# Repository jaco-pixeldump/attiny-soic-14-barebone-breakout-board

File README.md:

# ATtiny SOIC-14 Breadboard Breakout Board (tinyAVR-2 / 1 / 0 Series)

> [!NOTE]
> **Notice**: It's a work in progress, small changes are pending.

A compact, breadboard-friendly breakout adapter PCB for **14-pin SOIC Microchip ATtiny** microcontrollers (such as **ATtiny3224, ATtiny1624, ATtiny824, ATtiny424**, as well as 1-series and 0-series parts like **ATtiny1614, ATtiny814, ATtiny414, ATtiny404, ATtiny214, ATtiny204**).

Designed to bridge the gap between SMD SOIC-14 packaging and rapid breadboard prototyping, this board breaks out all 14 pins into a standard 600 mil DIP form factor with onboard decoupling capacitors for noise-free, stable operation.

---

## 3D Render

---

## Features

- **Breadboard Friendly (600 mil DIP Spacing)**: The two 7-pin header rows are spaced at 15.24 mm (0.6" / 600 mil), spanning the center divider of a standard solderless breadboard while leaving tie-points accessible on both sides.
- **Onboard Power Decoupling**:
  - `C1` (**10 nF**, 0805): High-frequency ceramic decoupling capacitor.
  - `C2` (**10 µF**, 0805): Bulk electrolytic/tantalum-replacement ceramic capacitor.
  - Placed directly across $V_{DD}$ (Pin 1) and $\text{GND}$ (Pin 14) to eliminate supply ripple, reduce voltage dips, and prevent brownout resets.
- **Direct 1:1 DIP Pinout**: Headers match the physical DIP-14 pin numbering (Pins 1–7 down the left row, Pins 8–14 down the right row).
- **UPDI Programming Access**: The single-wire UPDI interface on Pin 10 (`PA0 / ~RESET / UPDI`) is broken out directly, enabling instant flashing via SerialUPDI or hardware programmers.
- **Continuous Ground Plane**: Bottom layer is an uninterrupted copper ground pour for solid signal return paths and improved EMI performance.
- **Clear Silkscreen Markings**: Pin 1 orientation triangle, component references, GND reference, and board family indicators clearly printed.

---

## Board Specifications

| Parameter | Value |
|---|---|
| **Dimensions** | 21.06 mm × 19.60 mm (0.83" × 0.77") |
| **Layers** | 2 Layers (FR-4) |
| **Row Pitch** | 15.24 mm (0.600" / 600 mil DIP) |
| **Header Pitch** | 2.54 mm (0.100") |
| **IC Footprint** | SOIC-14 (3.9 mm × 8.7 mm, 1.27 mm pitch) |
| **Passive Footprint** | 0805 Metric (2012) with hand-solder pads |
| **Copper Weight** | 1 oz (35 µm) |
| **Default Board Thickness** | 1.6 mm |

---

## Pinout & Peripheral Mapping

The breakout headers map 1:1 to the SOIC-14 IC pins. The table below lists the pin functions for the modern **ATtiny tinyAVR 2-Series** (ATtiny3224 / ATtiny1624 / ATtiny824 / ATtiny424):

```
                       +---[ SOIC-14 / DIP-14 ]---+
        VDD (+1.8V..5V) [ 1  ]                    [ 14 ] GND
      PA4 (AIN4 / TCA0) [ 2  ]                    [ 13 ] PA3 (AIN3 / EXTCLK)
     PA5 (AIN5 / VREFA) [ 3  ]                    [ 12 ] PA2 (AIN2 / USART0 RX)
      PA6 (AIN6 / TCA0) [ 4  ]                    [ 11 ] PA1 (AIN1 / USART0 TX)
     PA7 (AIN7 / EVOUT) [ 5  ]                    [ 10 ] PA0 (UPDI / ~RESET)
 PB3 (RxD / SCL / TCB0) [ 6  ]                    [  9 ] PB0 (AIN11 / CLKOUT)
 PB2 (TxD / SDA / TCA0) [ 7  ]                    [  8 ] PB1 (AIN10 / TCA0)
                        +--------------------------+
```

### Detailed Pin Table

| Header Pin | IC Pin | Primary Name | Default / Alternate Functions | Notes |
|:---:|:---:|:---|:---|:---|
| **1** | 1 | `VDD` | Power supply (+1.8V to +5.5V) | Decoupled via C1 (10nF) and C2 (10µF) |
| **2** | 2 | `PA4` | AIN4, TCA0 WO4, CCL IN0, USART0 XCK | Digital I/O / Analog input |
| **3** | 3 | `PA5` | AIN5, TCA0 WO5, CCL OUT0, VREFA | Analog reference / PWM |
| **4** | 4 | `PA6` | AIN6, TCA0 WO0, CCL IN1, AC0 OUT | Analog input / PWM |
| **5** | 5 | `PA7` | AIN7, TCA0 WO1, CCL IN2, EVOUT0 | Event output / PWM |
| **6** | 6 | `PB3` | AIN8, TCA0 WO0, TCB0 WO, USART0 RXD, TWI0 SCL | I2C SCL / UART RX |
| **7** | 7 | `PB2` | AIN9, TCA0 WO1, USART0 TXD, TWI0 SDA | I2C SDA / UART TX |
| **8** | 8 | `PB1` | AIN10, TCA0 WO2, USART0 XCK | Digital I/O / Analog input |
| **9** | 9 | `PB0` | AIN11, TCA0 WO2, CLKOUT | Clock output / Analog input |
| **10** | 10 | `PA0` | `~RESET` / `UPDI` | **Programming / Debugging pin** |
| **11** | 11 | `PA1` | AIN1, TCA0 WO1, USART0 TXD | UART Alternate TX / Analog input |
| **12** | 12 | `PA2` | AIN2, TCA0 WO2, USART0 RXD, EVOUT1 | UART Alternate RX / Analog input |
| **13** | 13 | `PA3` | AIN3, TCA0 WO3, EXTCLK | External clock input / Analog input |
| **14** | 14 | `GND` | Ground reference (0V) | Common ground plane connection |

*(Note: Pin functions are also backwards-compatible with tinyAVR 0-series and 1-series SOIC-14 microcontrollers).*

---

## Bill of Materials (BOM)

| Reference | Value | Package / Footprint | Qty | Description | Suggested Part / MPN |
|---|---|---|:---:|---|---|
| **U1** | ATtiny3224-SS | SOIC-14 (3.9x8.7mm, 1.27mm pitch) | 1 | 8-bit AVR Microcontroller (20MHz, 32KB Flash, 3KB SRAM) | `ATTINY3224-SSFR` / `ATTINY1624-SSFR` |
| **C1** | 10 nF (0.01 µF) | 0805 (2012 Metric) | 1 | Ceramic capacitor, 50V, X7R (High-frequency decoupling) | Generic 0805 10nF 50V |
| **C2** | 10 µF | 0805 (2012 Metric) | 1 | Ceramic capacitor, 10V–25V, X5R/X7R (Bulk power stabilization) | Generic 0805 10µF 16V |
| **J1, J2** | 1x07 Pin Header | 2.54 mm Pitch THT (Vertical) | 2 | 7-pin male breakaway header | Standard 2.54 mm pin header |

A CSV format BOM is also available at [`hardware_docs/bom.csv`](hardware_docs/bom.csv).

---

## Schematic & Hardware Documentation

The schematic and board were authored in **KiCad 10**.

- **Vector Schematic**: [`hardware_docs/schematic.svg`](hardware_docs/schematic.svg)
- **Printable Schematic**: [`hardware_docs/schematic.pdf`](hardware_docs/schematic.pdf)

### Board Layout Preview

| Top Side (Components & Silkscreen) | Bottom Side (Ground Plane) |
|:---:|:---:|
|  |  |

---

## Fabrication & Ordering

Ready-to-order Gerbers and drill files are archived in **[`soic14-bb-gerbers.zip`](soic14-bb-gerbers.zip)**.

### Ordering with JLCPCB / PCBWay:
1. Download **`soic14-bb-gerbers.zip`**.
2. Upload the `.zip` file directly to the manufacturer's quote page (e.g., [JLCPCB](https://jlcpcb.com/) or [PCBWay](https://www.pcbway.com/)).
3. Select standard options:
   - **Dimensions**: ~21 mm × 19.6 mm (auto-detected)
   - **Layers**: 2
   - **PCB Thickness**: 1.6 mm
   - **Solder Mask**: Green (or your preferred color)
   - **Silkscreen**: White
   - **Surface Finish**: HASL (with lead) or Lead-Free HASL / ENIG
   - **Copper Weight**: 1 oz

Individual Gerber and Excellon drill files can also be inspected directly in [`to_pcb_providers/`](to_pcb_providers/).

---

## Programming with SerialUPDI

The ATtiny 2-series uses a single-wire UPDI interface on Pin 10 (`PA0`). You can program it easily using any USB-to-UART bridge (FTDI, CH340, CP2102) with a resistor or diode:

```
 USB-to-Serial
  Adapter                 ATtiny Breakout
+---------+              +---------------+
|     TXD |----+         |               |
|         |   [4.7kΩ]    |               |
|         |    +-------->| Pin 10 (UPDI) |
|     RXD |----+         |               |
|     GND |------------->| Pin 14 (GND)  |
|     VCC |------------->| Pin 1  (VDD)  |
+---------+              +---------------+
```

### PlatformIO Configuration Example

Using [`megaTinyCore`](https://github.com/SpenceKonde/megaTinyCore) via PlatformIO:

```ini
[env:attiny3224]
platform = atmelmegaavr
board = ATtiny3224
framework = arduino

; SerialUPDI upload configuration
upload_protocol = serialupdi
upload_port = /dev/ttyUSB0   ; Or COMx on Windows
upload_flags =
    -b
    115200
```

---

## Repository Structure

```
├── hardware_docs/              # High-resolution documentation assets
│   ├── bom.csv                 # Exported Bill of Materials
│   ├── pcb_3d.png              # 3D isometric board render
│   ├── pcb_top.png             # 2D top layer render
│   ├── pcb_bottom.png          # 2D bottom layer render
│   ├── schematic.pdf           # Printable schematic document
│   └── schematic.svg           # High-resolution vector schematic
├── to_pcb_providers/           # Pre-generated Gerber and drill files
│   ├── soic14-bb-B_Cu.gbr
│   ├── soic14-bb-B_Mask.gbr
│   ├── soic14-bb-B_Paste.gbr
│   ├── soic14-bb-B_Silkscreen.gbr
│   ├── soic14-bb-Edge_Cuts.gbr
│   ├── soic14-bb-F_Cu.gbr
│   ├── soic14-bb-F_Mask.gbr
│   ├── soic14-bb-F_Paste.gbr
│   ├── soic14-bb-F_Silkscreen.gbr
│   ├── soic14-bb-job.gbrjob
│   ├── soic14-bb-NPTH.drl
│   └── soic14-bb-PTH.drl
├── .gitignore                  # KiCad & OS ignore rules
├── LICENSE                     # MIT License
├── README.md                   # Project documentation (this file)
├── soic14-bb-gerbers.zip       # Ready-to-upload manufacturer ZIP archive
├── soic14-bb.kicad_pcb         # KiCad PCB board file
├── soic14-bb.kicad_pro         # KiCad project definition
└── soic14-bb.kicad_sch         # KiCad schematic design
```

---

## License

This project is open-source hardware licensed under the [MIT License](LICENSE).
Feel free to build, modify, fabricate, and distribute!

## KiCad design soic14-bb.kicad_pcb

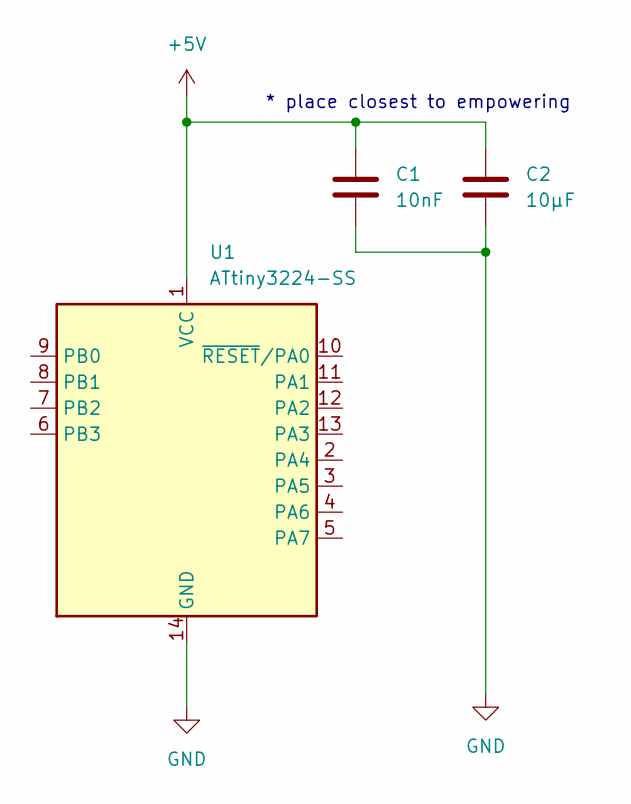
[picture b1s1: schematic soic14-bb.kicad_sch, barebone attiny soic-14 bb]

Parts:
C1: 10nF; C_0805_2012Metric_Pad1.18x1.45mm_HandSolder
C2: 10µF; C_0805_2012Metric_Pad1.18x1.45mm_HandSolder
U1: ATtiny3224-SS; SOIC-14_3.9x8.7mm_P1.27mm

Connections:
+5V: C1.1, C2.1, U1.1 (VCC)
GND: C1.2, C2.2, U1.14 (GND)

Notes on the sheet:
* place closest to empowering

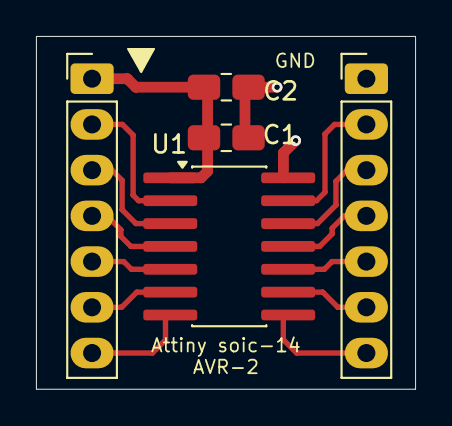
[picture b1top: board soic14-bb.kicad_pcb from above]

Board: 2 copper layers, 21.1 x 19.6 mm, 3 parts (0 on the bottom side), 2 nets.

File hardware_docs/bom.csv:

"Refs","Value","Footprint","Qty","DNP"
"C1","10nF","Capacitor_SMD:C_0805_2012Metric_Pad1.18x1.45mm_HandSolder","1",""
"C2","10µF","Capacitor_SMD:C_0805_2012Metric_Pad1.18x1.45mm_HandSolder","1",""
"U1","ATtiny3224-SS","Package_SO:SOIC-14_3.9x8.7mm_P1.27mm","1",""
